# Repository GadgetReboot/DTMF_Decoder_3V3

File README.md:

# DTMF_Decoder_3V3
MT88L70 based DTMF decoder with 3.3v power/logic
<br><br><BR><BR>
This DTMF decoder uses the MT88L70, powered by 3.3v and interfacing with 3.3v GPIO to decode the touch tone keys.<BR>
It has an RJ phone jack and 600:600 transformer to connect to a phone line to pick up audio, listening for DTMF tone pairs.<BR><BR>
Note: It is recommended to only connect this circuit to a phone line after it is taken off hook to keep the AC voltages low, such as audio signals and not a high voltage ring signal.
This can be achieved by switching the circuit into the phone line with a relay.

This circuit has only been tested on a simulated phone line in a workshop environment and is not guaranteed to meet official telephone line specifications.

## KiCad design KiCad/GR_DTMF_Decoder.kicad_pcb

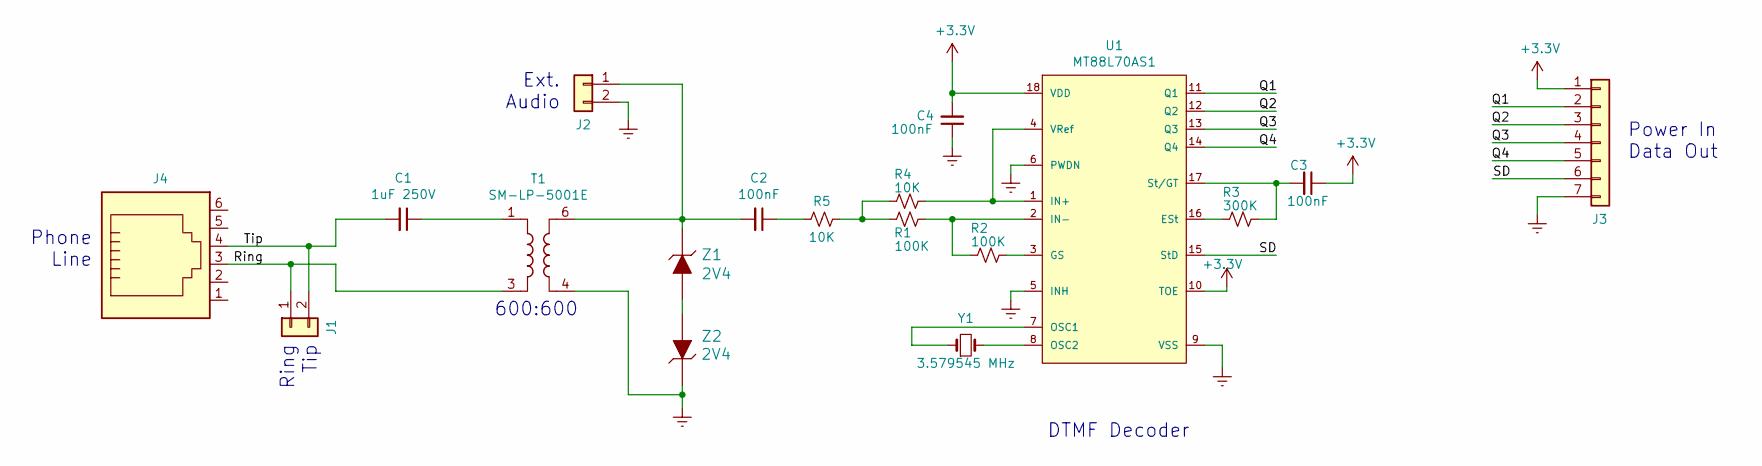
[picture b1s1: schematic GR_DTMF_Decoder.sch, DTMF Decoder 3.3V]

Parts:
C1: 1uF 250V; C_Rect_L18.0mm_W8.0mm_P15.00mm_FKS3_FKP3
C2, C3, C4: 100nF; C_0805_2012Metric_Pad1.15x1.40mm_HandSolder
J1, J2: Conn_01x02; PinHeader_1x02_P2.54mm_Vertical
J3: Conn_01x07; PinHeader_1x07_P2.54mm_Vertical
J4: RJ12; RJ_6p6c
R1, R2: 100K; R_0805_2012Metric_Pad1.15x1.40mm_HandSolder
R3: 300K; R_0805_2012Metric_Pad1.15x1.40mm_HandSolder
R4, R5: 10K; R_0805_2012Metric_Pad1.15x1.40mm_HandSolder
T1: SM-LP-5001E; Transformer_SMLP5001
U1: MT88L70AS1; SOIC-18W_7.5x11.6mm_P1.27mm
Y1: 3.579545 MHz; Crystal_SMD_HC49-SD_HandSoldering
Z1, Z2: 2V4; Zener_MiniMELF; MPN ZMM3.3; Digi-Key_PN Diotec Semiconductor

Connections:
+3V3: C3.1, C4.2, J3.1, U1.10 (TOE), U1.18 (VDD)
/Q1: J3.2, U1.11 (Q1)
/Q2: J3.3, U1.12 (Q2)
/Q3: J3.4, U1.13 (Q3)
/Q4: J3.5, U1.14 (Q4)
/Ring: J1.1, J4.3, T1.3
/SD: J3.6, U1.15 (StD)
/Tip: C1.2, J1.2, J4.4
GNDREF: C4.1, J2.2, J3.7, T1.4, U1.5 (INH), U1.6 (PWDN), U1.9 (VSS), Z2.K
unnamed: C1.1, T1.1
unnamed: C2.1, R5.2
unnamed: C2.2, J2.1, T1.6, Z1.K
unnamed: C3.2, R3.1, U1.17 (St/GT)
unnamed: R1.1, R2.2, U1.2 (IN-)
unnamed: R1.2, R4.1, R5.1
unnamed: R2.1, U1.3 (GS)
unnamed: R3.2, U1.16 (ESt)
unnamed: R4.2, U1.1 (IN+), U1.4 (VRef)
unnamed: U1.7 (OSC1), Y1.1
unnamed: U1.8 (OSC2), Y1.2
unnamed: Z1.A, Z2.A

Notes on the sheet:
DTMF Decoder
Power In Data Out
Phone Line
Ext. Audio
600:600
Ring
Tip

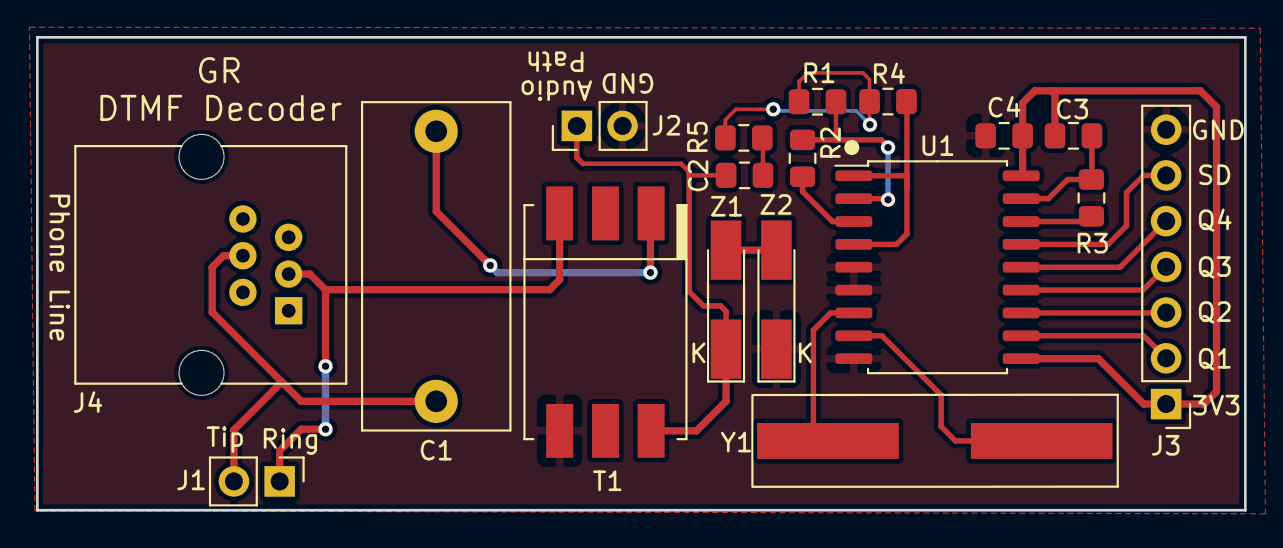
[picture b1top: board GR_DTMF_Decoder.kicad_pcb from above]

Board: 2 copper layers, 67.1 x 26.3 mm, 18 parts (0 on the bottom side), 21 nets.
